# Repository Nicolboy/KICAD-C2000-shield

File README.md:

# KICAD-C2000-shield

Shield d'isolation et cartes devkit pour TMS320 C2000, conçus sous KiCad 10.
Le brochage est décrit en Markdown, les symboles et les projets KiCad en sont
**générés** — le document reste la source de vérité, pas le schéma.

Cible : une commande numérique de convertisseur de puissance isolé, pilotée par
un C2000 et supervisée par un ESP32-C6 pour le Wi-Fi et la mise à jour FOTA.

---

## Architecture — quatre cartes, une barrière

| Carte | Rôle |
|---|---|
| **Puissance** | Conversion, barrière d'isolation, isolateurs (AMC0311S, AMC0300R, ISO7710, DPC817), shunts en connexion Kelvin, régulateurs |
| **Shield** | Support mécanique des deux devkits, adaptation de brochage, conditionnement analogique, protections. **Aucun composant isolé** |
| **Devkit C2000** | MCU, deux LDO 3,3 V, JTAG, bouton reset, LED, cavalier de boot |
| **Devkit ESP32** | Wi-Fi, hôte FOTA, écran OLED en SPI |

L'isolation est entièrement confinée à la carte de puissance. Le shield ne fait
que du conditionnement côté froid : c'est ce qui permet de le fabriquer en
2 couches à la maison sans se poser de question de ligne de fuite.

Liaison shield ↔ puissance : quatre nappes 2 × 8 à **alternance signal / masse
stricte 1:1**, aucune alimentation dedans. Le +5 V passe par un connecteur
séparé — les 500 mA de la commande n'ont pas à partager leur retour avec les
masses de référence des voies ADC.

---

## Le point de conception le plus notable

**Le connecteur est identique à 100 % entre le F280037 et le F28P551**, 56
positions sur 56. Les deux devkits sont interchangeables sur le shield.

Ce n'est pas une coïncidence, c'est le résultat d'un arbitrage : les LED ont été
délibérément posées sur les **entrées/sorties non communes** aux deux boîtiers,
pour que toutes les broches qui traversent le connecteur, elles, soient
communes. Les quatre divergences restent locales à la carte devkit :

| Broche | F280037 | F28P551 |
|---|---|---|
| 27 | VDD 1,2 V | LED bleue (GPIO20) |
| 28 | VDDIO 3,3 V | LED rouge (GPIO21) |
| 40 | LED rouge (GPIO32) | pastille de test |
| 46 | LED bleue (GPIO39) | VREGENZ à VSS |

La cause profonde est le régulateur 1,2 V : le F28P551 a le sien en interne,
activé par VREGENZ à VSS ; le F280037 en 64 PM non-Q n'a pas cette broche et
demande un LDO supplémentaire.

---

## Le brochage est du code

Le fichier [`doc/spec-devkit.md`](doc/spec-devkit.md) fait autorité. Les
symboles KiCad, les schémas et les vérifications en découlent par génération —
on ne modifie jamais un `.kicad_sym` à la main.

```
doc/spec-devkit.md            source de vérité, relue par un humain
        │
        ├── gen_symbole_mcu.py   → build/C2000_MCU_LQFP64.kicad_sym
        │                          (dimensionne le symbole depuis les noms)
        │
        └── gen_devkit.py        → devkit_A_F280037.*  devkit_B_F28P551.*
              ▲                    kicad_gen.py — primitives communes
              │
            src/*.kicad_sch        schémas source des devkits, versionnés

shield.*                       édité à la main dans KiCad — pas généré
```

L'intérêt n'est pas le gain de temps, c'est que **les règles de conception
deviennent exécutables**. Les générateurs vérifient ce que le document promet :
unicité des broches et des GPIO, masse de part et d'autre des voies de mesure de
courant, présence des réserves. Une divergence entre l'intention et le schéma
est une erreur de script, pas un oubli qu'on découvre au routage.

`gen_symbole_mcu.py` dimensionne par exemple le corps du symbole à partir de la
longueur réelle du nom de broche le plus long, pour que les textes des quatre
faces ne se croisent jamais — plutôt qu'une taille choisie à l'œil qui casse au
premier nom un peu long.

Les schémas ne contiennent d'ailleurs **aucun fil** : toute la connectivité
passe par des étiquettes globales posées sur le point de connexion de chaque
broche. C'est ce qui permet d'ajouter un composant par script sans rien router.

---

## Concevoir avec un agent

Une part inhabituelle du travail est faite par un agent : lire les datasheets,
en extraire les contraintes, écrire la spécification, générer les symboles,
poser les composants et choisir les boîtiers. **Le placement et le routage
restent manuels** — ils encodent des choix que rien ne devine sur une chaîne de
mesure de courant.

[`doc/methode-kicad-claude.md`](doc/methode-kicad-claude.md) documente cette
façon de travailler : le partage des rôles, le déroulé d'une séance, et surtout
les pièges de format rencontrés — chacun avec sa signature, parce que KiCad
répond « échec du chargement » et rien de plus quand un fichier est malformé.

---

## Projets KiCad

Trois, pas un de plus.

| Projet | Contenu |
|---|---|
| `shield.*` | Shield, connecteurs devkit 2 × 28, quatre nappes, ESP32-C6 |
| `devkit_A_F280037.*` | Devkit TMS320F280037CSPM |
| `devkit_B_F28P551.*` | Devkit TMS320F28P551SG5PM |

---

## Reproduire

KiCad 10 et Python 3.12 requis. `kicad-cli` doit être dans le `PATH`.

```bash
python gen_symbole_mcu.py -o build/     # symboles MCU
python gen_devkit.py --force            # les deux projets devkit

kicad-cli sch erc --exit-code-violations <projet>.kicad_sch
kicad-cli pcb drc --exit-code-violations <projet>.kicad_pcb
```

`shield.*` n'apparaît pas ici : il est édité à la main et ne se régénère pas.
Les schémas de devkit produits à la racine sont en revanche **jetables** — toute
retouche manuelle y est perdue au prochain `--force`. Ce qui doit survivre se
modifie dans `src/` ou dans le générateur.

Chaque carte existe en **deux versions de fabrication** : 2 couches gravées à
la maison — pistes 1 mm, vias 2 mm, perçage 0,8 mm — pour itérer vite sur la
mécanique, et 4 couches en fabrication externe, avec plan de masse continu sous
la zone analogique. Même schéma, même brochage, seul le PCB change.

---

## État d'avancement

Travail en cours, et le dire plutôt que de le masquer :

- **Schémas** — connecteurs posés, alimentations câblées avec `PWR_FLAG` par
  net. Le routage des signaux n'est pas fait : il demande des choix de
  conception qui n'ont pas leur place dans un générateur. D'où les
  `pin_not_connected` encore présents à l'ERC.
- **PCB** — non routés. Le DRC passe à 0 sur les trois projets, ce qui ne prouve
  rien tant qu'il n'y a pas de piste.
- **Carte de puissance** — spécifiée dans `doc/`, pas encore dessinée.

Les points laissés ouverts — caractéristiques de sortie des AMC, courant
d'entrée du REFIN, choix de VREFHI — sont listés en fin de
[`doc/decisions.md`](doc/decisions.md). Ils attendent une lecture de datasheet,
pas une estimation.

---

## Décisions à ne pas défaire

Certains choix ressemblent à des inefficacités sans en être. Les douze sont
documentés dans [`doc/decisions.md`](doc/decisions.md), chacun avec sa raison et
ce qui casse si on le défait — entre autres :

- Les **PWM3 et PWM4 restent en réserve et restent des PWM** : ce sont les deux
  seules paires complémentaires HRPWM avec temps mort matériel disponibles.
- Chaque shunt sort **deux fois**, `_MES` filtré et `_CMP` direct. Le chemin
  comparateur attaque le CMPSS sans filtre anti-repliement : pas de retard sur
  le déclenchement de la Trip Zone, et un défaut du filtre ne désarme pas la
  protection.
- Les **16 voies ADC sortent toutes** pour 9 nécessaires, les 5 libres étant
  câblées jusqu'aux réserves de nappe. Une voie ajoutée plus tard se raccorde
  sans retoucher une seule carte.

---

## Licence

[CERN-OHL-S v2](LICENSE) — CERN Open Hardware Licence, fortement réciproque.

Tu peux étudier, modifier, fabriquer et distribuer ce matériel. En contrepartie,
si tu distribues un produit fondé dessus, ou une version modifiée, tu dois
publier les sources correspondantes sous la même licence.

C'est la licence de référence du matériel libre, l'équivalent de la GPL côté
logiciel. Si tu préfères une réciprocité limitée à la carte elle-même, ou pas de
réciprocité du tout, les variantes CERN-OHL-W et CERN-OHL-P existent.

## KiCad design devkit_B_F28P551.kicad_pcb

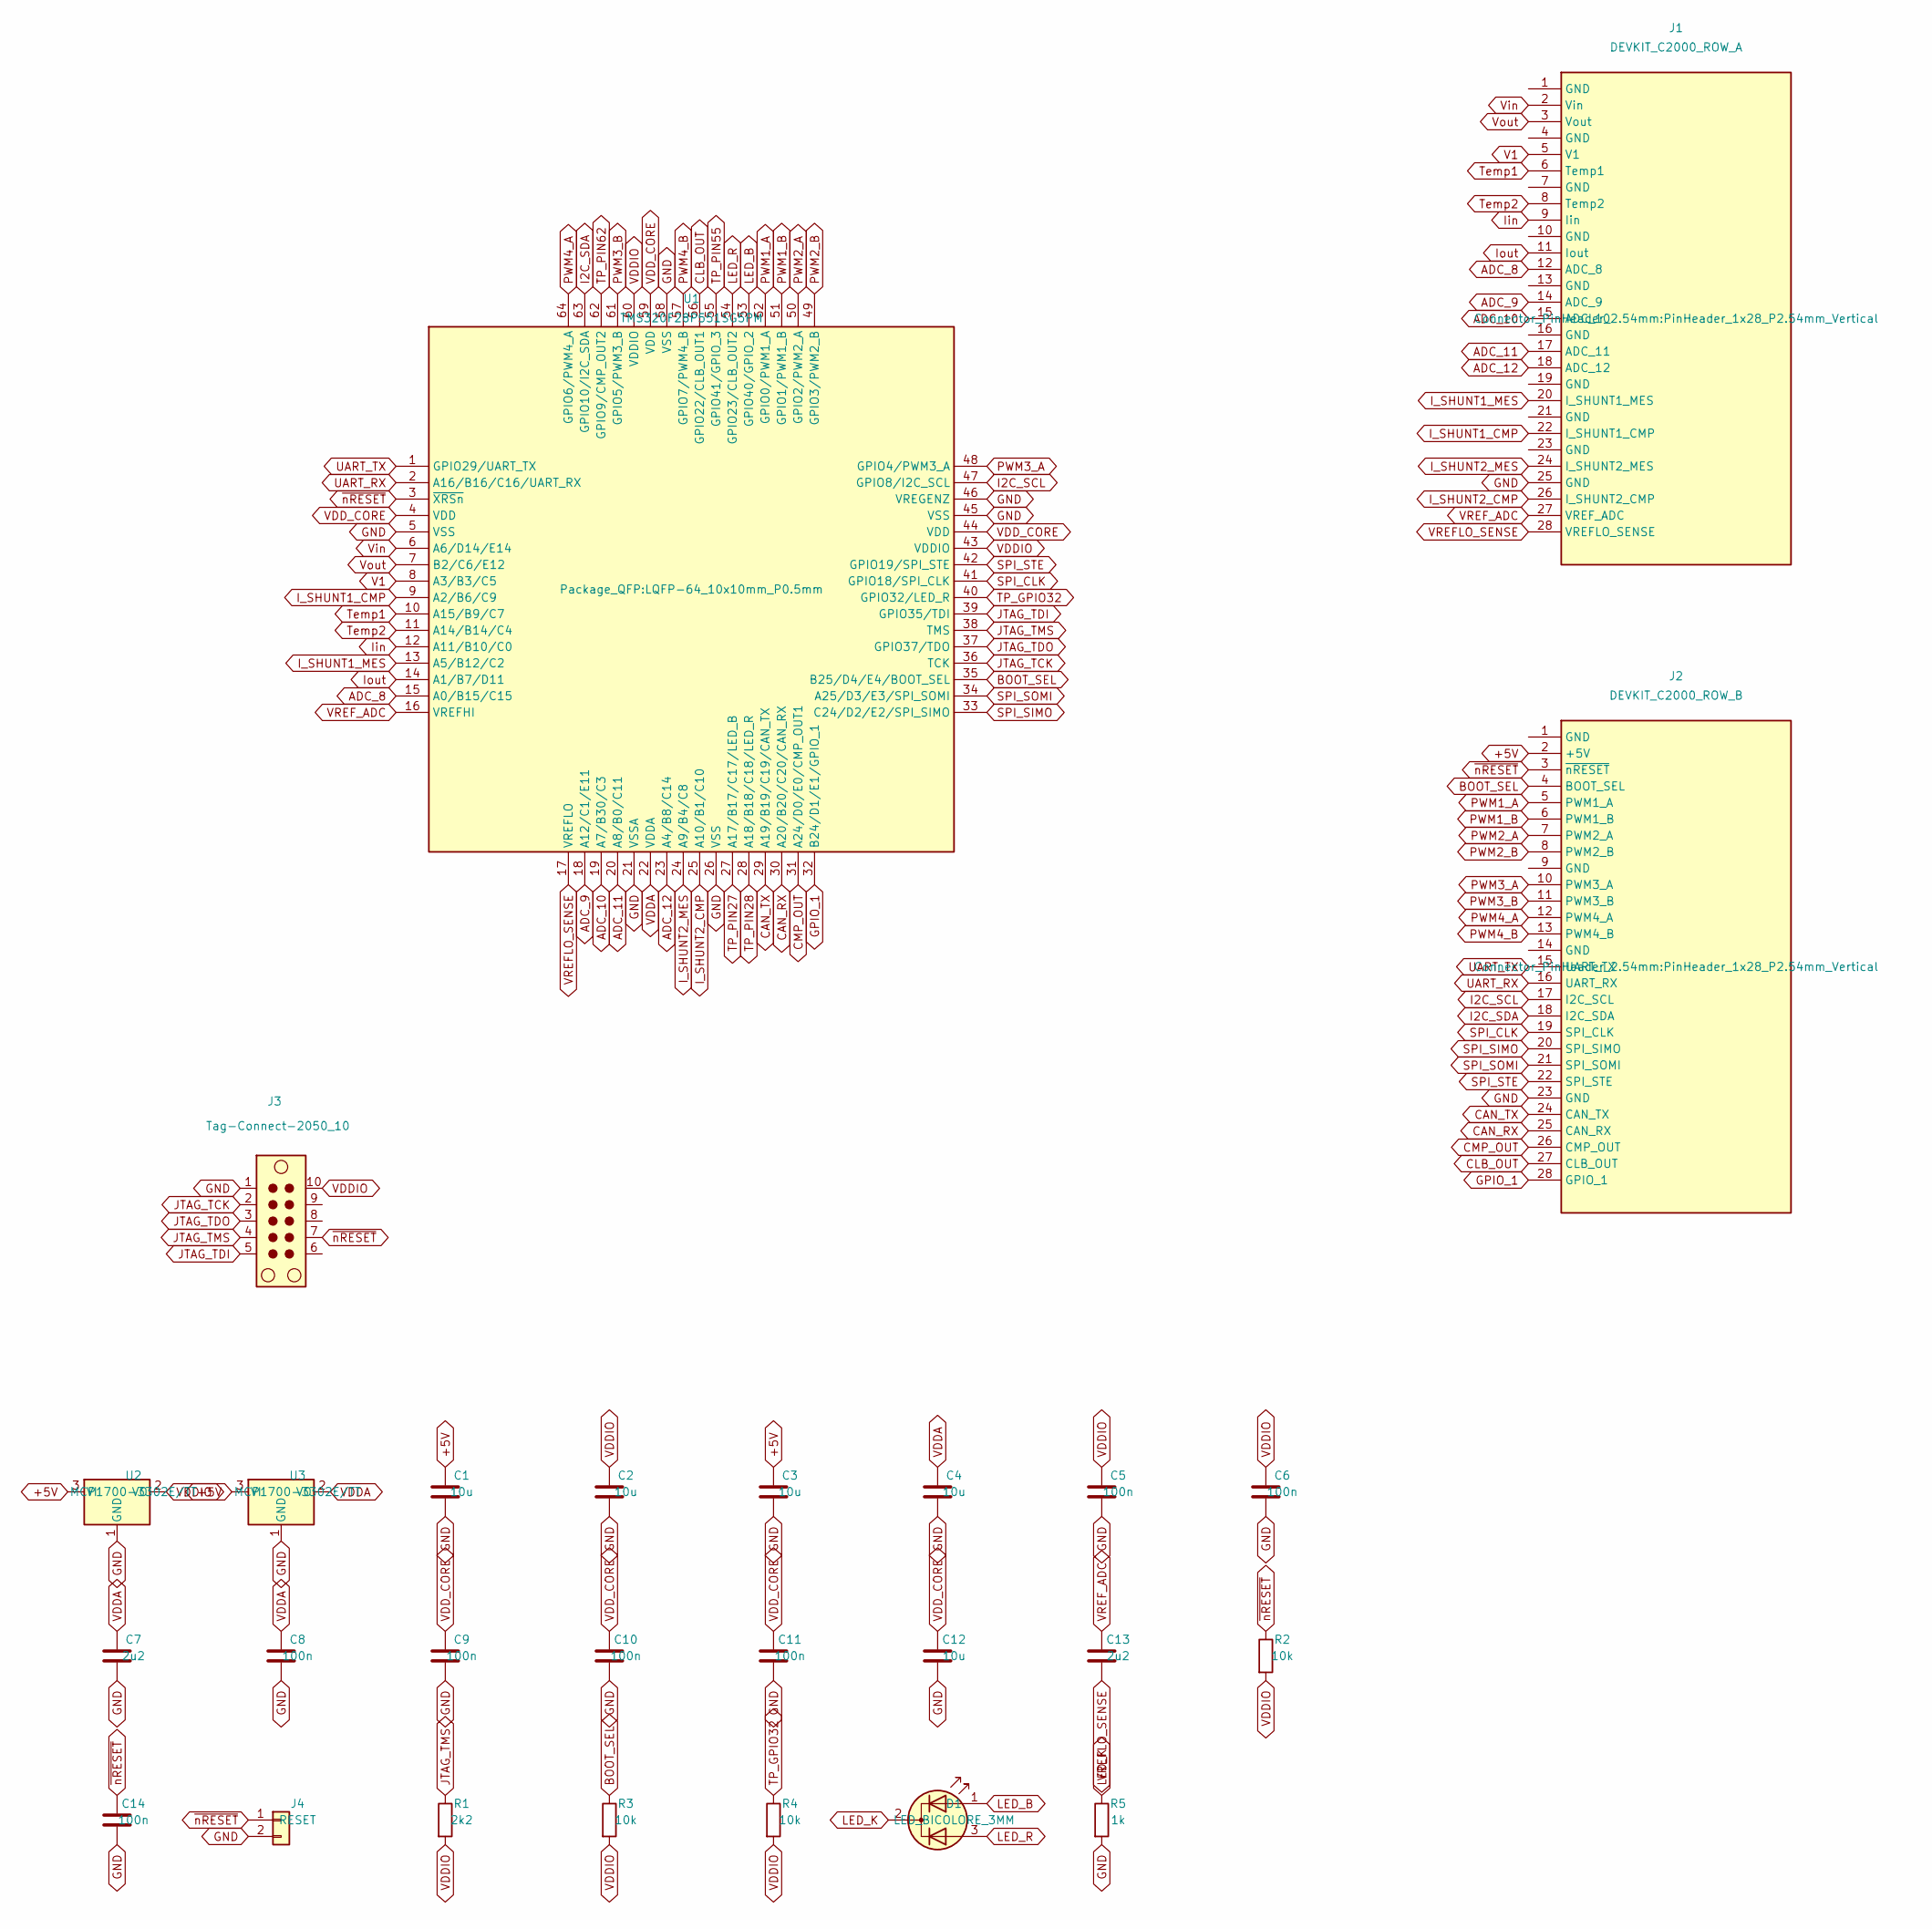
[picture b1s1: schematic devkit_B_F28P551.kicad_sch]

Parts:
C1, C2, C3, C4, C12: 10u; C_0805_2012Metric
C5, C6, C8, C9, C10, C11, C14: 100n; C_0805_2012Metric
C7, C13: 2u2; C_0805_2012Metric
D1: LED_BICOLORE_3MM; LED_D3.0mm-3
J1: DEVKIT_C2000_ROW_A; PinHeader_1x28_P2.54mm_Vertical
J2: DEVKIT_C2000_ROW_B; PinHeader_1x28_P2.54mm_Vertical
J3: Tag-Connect-2050_10; Tag-Connect_TC2050-IDC-NL_2x05_P1.27mm_Vertical
J4: RESET; PinHeader_1x02_P2.54mm_Vertical
R1: 2k2; R_0805_2012Metric
R2, R3, R4: 10k; R_0805_2012Metric
R5: 1k; R_0805_2012Metric
U1: TMS320F28P551SG5PM; LQFP-64_10x10mm_P0.5mm
U2, U3: MCP1700-3302E/TT; SOT-23

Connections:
+5V: C1.1, C3.1, J2.2 (+5V), U2.3 (VI), U3.3 (VI)
ADC_8: J1.12 (ADC_8), U1.15 (A0/B15/C15)
ADC_9: J1.14 (ADC_9), U1.18 (A12/C1/E11)
ADC_10: J1.15 (ADC_10), U1.19 (A7/B30/C3)
ADC_11: J1.17 (ADC_11), U1.20 (A8/B0/C11)
ADC_12: J1.18 (ADC_12), U1.23 (A4/B8/C14)
BOOT_SEL: J2.4 (BOOT_SEL), R3.1, U1.35 (B25/D4/E4/BOOT_SEL)
CAN_RX: J2.25 (CAN_RX), U1.30 (A20/B20/C20/CAN_RX)
CAN_TX: J2.24 (CAN_TX), U1.29 (A19/B19/C19/CAN_TX)
CLB_OUT: J2.27 (CLB_OUT), U1.56 (GPIO22/CLB_OUT1)
CMP_OUT: J2.26 (CMP_OUT), U1.31 (A24/D0/E0/CMP_OUT1)
GND: C1.2, C2.2, C3.2, C4.2, C5.2, C6.2, C7.2, C8.2, C9.2, C10.2, C11.2, C12.2, C14.2, J1.25 (GND), J2.23 (GND), J3.1, J4.2, R5.2, U1.5 (VSS), U1.21 (VSSA), U1.26 (VSS), U1.45 (VSS), U1.46 (VREGENZ), U1.58 (VSS), U2.1 (GND), U3.1 (GND)
GPIO_1: J2.28 (GPIO_1), U1.32 (B24/D1/E1/GPIO_1)
I2C_SCL: J2.17 (I2C_SCL), U1.47 (GPIO8/I2C_SCL)
I2C_SDA: J2.18 (I2C_SDA), U1.63 (GPIO10/I2C_SDA)
I_SHUNT1_CMP: J1.22 (I_SHUNT1_CMP), U1.9 (A2/B6/C9)
I_SHUNT1_MES: J1.20 (I_SHUNT1_MES), U1.13 (A5/B12/C2)
I_SHUNT2_CMP: J1.26 (I_SHUNT2_CMP), U1.25 (A10/B1/C10)
I_SHUNT2_MES: J1.24 (I_SHUNT2_MES), U1.24 (A9/B4/C8)
Iin: J1.9 (Iin), U1.12 (A11/B10/C0)
Iout: J1.11 (Iout), U1.14 (A1/B7/D11)
JTAG_TCK: J3.2, U1.36 (TCK)
JTAG_TDI: J3.5, U1.39 (GPIO35/TDI)
JTAG_TDO: J3.3, U1.37 (GPIO37/TDO)
JTAG_TMS: J3.4, R1.1, U1.38 (TMS)
LED_B: D1.1 (A1), U1.53 (GPIO40/GPIO_2)
LED_K: D1.2 (K), R5.1
LED_R: D1.3 (A2), U1.54 (GPIO23/CLB_OUT2)
PWM1_A: J2.5 (PWM1_A), U1.52 (GPIO0/PWM1_A)
PWM1_B: J2.6 (PWM1_B), U1.51 (GPIO1/PWM1_B)
PWM2_A: J2.7 (PWM2_A), U1.50 (GPIO2/PWM2_A)
PWM2_B: J2.8 (PWM2_B), U1.49 (GPIO3/PWM2_B)
PWM3_A: J2.10 (PWM3_A), U1.48 (GPIO4/PWM3_A)
PWM3_B: J2.11 (PWM3_B), U1.61 (GPIO5/PWM3_B)
PWM4_A: J2.12 (PWM4_A), U1.64 (GPIO6/PWM4_A)
PWM4_B: J2.13 (PWM4_B), U1.57 (GPIO7/PWM4_B)
SPI_CLK: J2.19 (SPI_CLK), U1.41 (GPIO18/SPI_CLK)
SPI_SIMO: J2.20 (SPI_SIMO), U1.33 (C24/D2/E2/SPI_SIMO)
SPI_SOMI: J2.21 (SPI_SOMI), U1.34 (A25/D3/E3/SPI_SOMI)
SPI_STE: J2.22 (SPI_STE), U1.42 (GPIO19/SPI_STE)
TP_GPIO32: R4.1, U1.40 (GPIO32/LED_R)
TP_PIN27: U1.27 (A17/B17/C17/LED_B)
TP_PIN28: U1.28 (A18/B18/C18/LED_R)
TP_PIN55: U1.55 (GPIO41/GPIO_3)
TP_PIN62: U1.62 (GPIO9/CMP_OUT2)
Temp1: J1.6 (Temp1), U1.10 (A15/B9/C7)
Temp2: J1.8 (Temp2), U1.11 (A14/B14/C4)
UART_RX: J2.16 (UART_RX), U1.2 (A16/B16/C16/UART_RX)
UART_TX: J2.15 (UART_TX), U1.1 (GPIO29/UART_TX)
V1: J1.5 (V1), U1.8 (A3/B3/C5)
VDDA: C4.1, C7.1, C8.1, U1.22 (VDDA), U3.2 (VO)
VDDIO: C2.1, C5.1, C6.1, J3.10, R1.2, R2.2, R3.2, R4.2, U1.43 (VDDIO), U1.60 (VDDIO), U2.2 (VO)
VDD_CORE: C9.1, C10.1, C11.1, C12.1, U1.4 (VDD), U1.44 (VDD), U1.59 (VDD)
VREFLO_SENSE: C13.2, J1.28 (VREFLO_SENSE), U1.17 (VREFLO)
VREF_ADC: C13.1, J1.27 (VREF_ADC), U1.16 (VREFHI)
Vin: J1.2 (Vin), U1.6 (A6/D14/E14)
Vout: J1.3 (Vout), U1.7 (B2/C6/E12)
~nRESET: C14.1, J2.3 (~nRESET), J3.7, J4.1, R2.1, U1.3 (~XRSn)

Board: 2 copper layers, 27 parts (0 on the bottom side), 54 nets, no tracks yet.

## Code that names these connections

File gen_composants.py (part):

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#
# Les valeurs de net sont les etiquettes globales deja presentes dans les
# schemas : VDDIO, VDDA, VDD_CORE, GND, +5V, LED_B, LED_R, BOOT_SEL,
# TP_GPIO32, VREF_ADC, VREFLO_SENSE, JTAG_TMS, ~{nRESET}.
# --------------------------------------------------------------------------

R = "Device:R"
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    ("R1", R, "2k2", FP_R, {"1": "JTAG_TMS", "2": "VDDIO"}),

    # --- selection du mode de boot ----------------------------------------
    # SPRSPC5 table 7-8 : Flash demande GPIO24 = 1 ET GPIO32 = 1. Et la
    # section 5.5 precise que les rappels internes des GPIO sont desactives
    # pendant le boot. Sans ces deux resistances le mode de demarrage est
    # indetermine, Parallel IO compris. Pas de cavalier : Flash seul suffit,
    # le chargement en RAM passe par le JTAG.
    ("R3", R, "10k", FP_R, {"1": "BOOT_SEL", "2": "VDDIO"}),
    ("R4", R, "10k", FP_R, {"1": "TP_GPIO32", "2": "VDDIO"}),

    # --- signalisation ----------------------------------------------------
    # LED 3 mm bicolore a cathode commune. Une seule resistance sur la
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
